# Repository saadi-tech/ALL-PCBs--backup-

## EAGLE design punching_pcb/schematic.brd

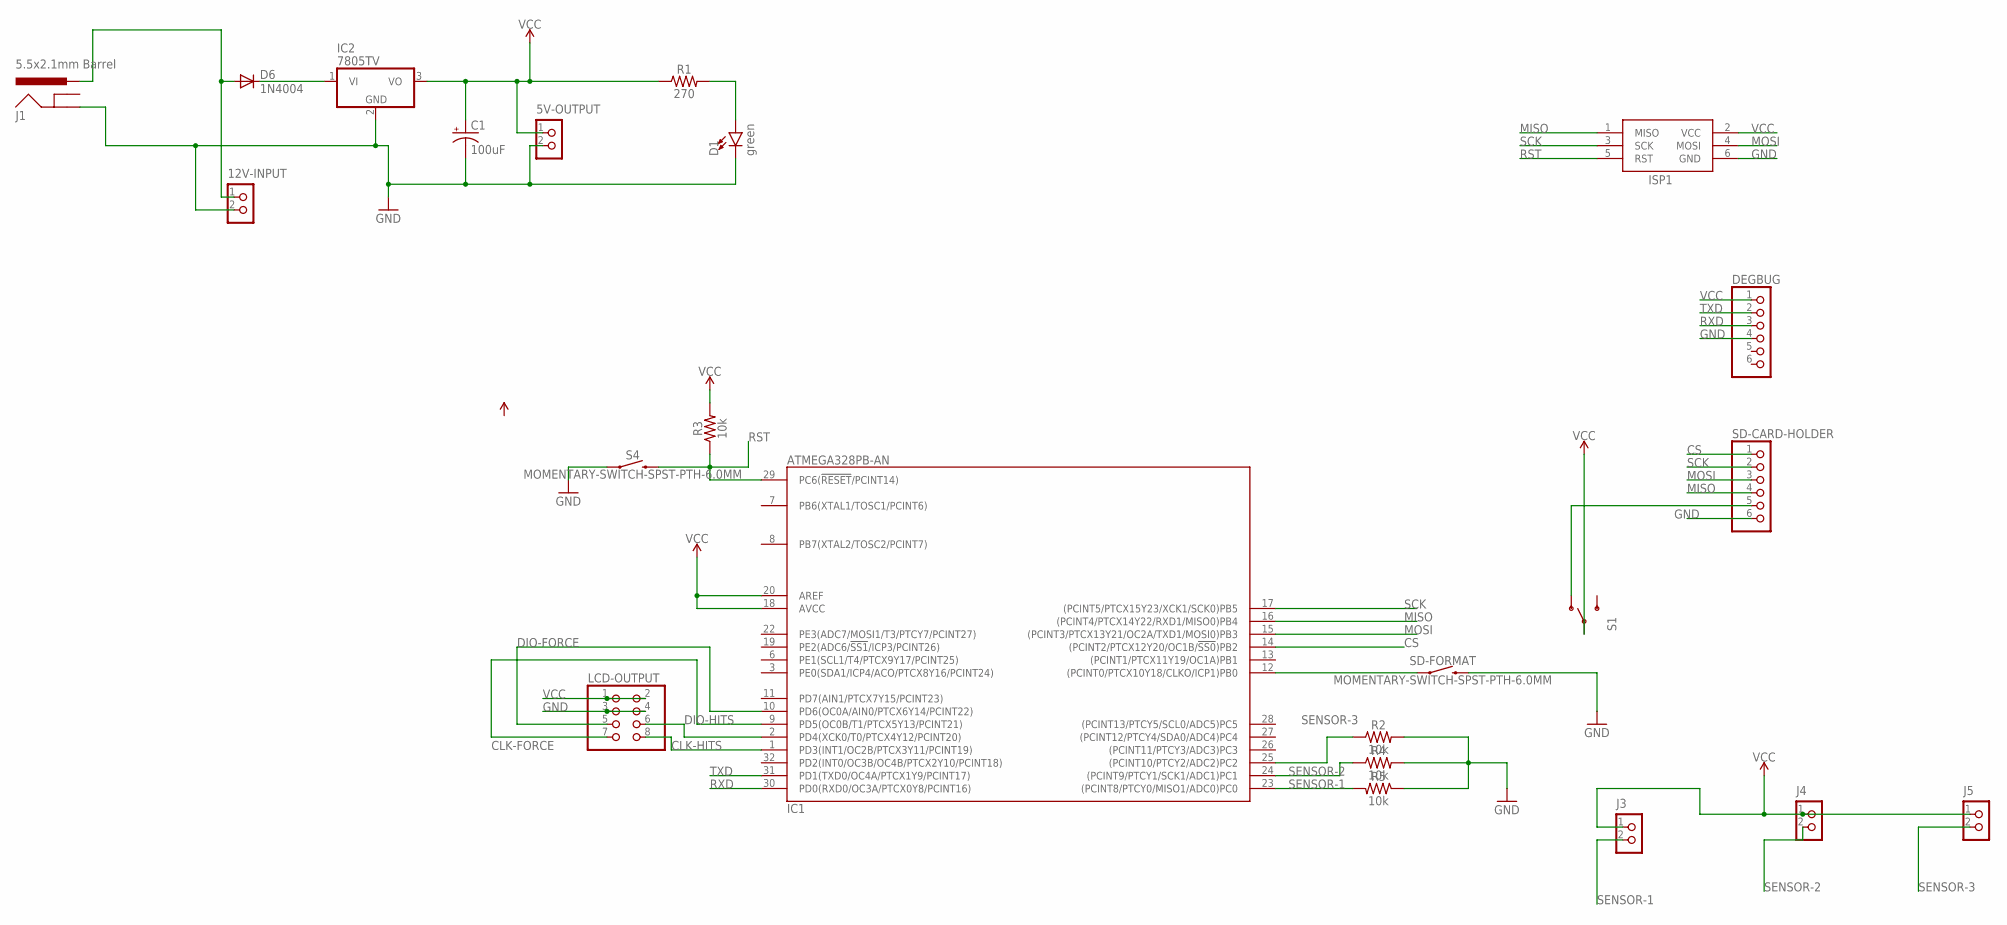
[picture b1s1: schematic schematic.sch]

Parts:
5V-OUTPUT, 12V-INPUT: CON_TERMINAL_BLOCK_02-5MM; TERMINAL_BLOCK_2P_5
C1: 100uF; CPOL-RADIAL-2.5MM-6.5MM
D1: green; LED-1206
D6: 1N4004; DO41-10
DEGBUG: PINHD-1X6; 1X06
IC1: ATMEGA328PB-AN; QFP32_7X7_0.80
IC2: 7805TV; TO220V
ISP1: AVRISP-6; AVRISP
J1: 5.5x2.1mm Barrel; POWER_JACK_SMD
J3, J4, J5: CON_TERMINAL_BLOCK_02-5MM; TERMINAL_BLOCK_2P_5
LCD-OUTPUT: PINHD-2X4; 2X04
R1: 270; 1206
R2, R3, R4, R5: 10k; 1206
S1: SWITCH-SPDTSMD; SWITCH_SPDT_SMD
S4: MOMENTARY-SWITCH-SPST-PTH-6.0MM; TACTILE_SWITCH_PTH_6.0MM
SD-CARD-HOLDER: PINHD-1X6; 1X06
SD-FORMAT: MOMENTARY-SWITCH-SPST-PTH-6.0MM; TACTILE_SWITCH_PTH_6.0MM

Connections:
CLK-FORCE: IC1.9 (PD5(OC0B/T1/PTCX5Y13/PCINT21)), LCD-OUTPUT.7
CLK-HITS: IC1.1 (PD3(INT1/OC2B/PTCX3Y11/PCINT19)), LCD-OUTPUT.8
CS: IC1.14 ((PCINT2/PTCX12Y20/OC1B/!SS0!)PB2), SD-CARD-HOLDER.1
DIO-FORCE: IC1.10 (PD6(OC0A/AIN0/PTCX6Y14/PCINT22)), LCD-OUTPUT.5
DIO-HITS: IC1.2 (PD4(XCK0/T0/PTCX4Y12/PCINT20)), LCD-OUTPUT.6
GND: 5V-OUTPUT.2, 12V-INPUT.2, C1.2 (-), D1.C, DEGBUG.4, IC1.5 (GND), IC1.21 (GND), IC2.2 (GND), ISP1.6 (GND), J1.P$4 (GND), LCD-OUTPUT.3, LCD-OUTPUT.4, R2.2, R4.2, R5.1, S4.1, SD-CARD-HOLDER.6, SD-FORMAT.3 (2)
MISO: IC1.16 ((PCINT4/PTCX14Y22/RXD1/MISO0)PB4), ISP1.1 (MISO), SD-CARD-HOLDER.4
MOSI: IC1.15 ((PCINT3/PTCX13Y21/OC2A/TXD1/MOSI0)PB3), ISP1.4 (MOSI), SD-CARD-HOLDER.3
unnamed: D1.A, R1.2
unnamed: IC1.12 ((PCINT0/PTCX10Y18/CLKO/ICP1)PB0), SD-FORMAT.1
unnamed: 12V-INPUT.1, D6.A, J1.VIN0 (PWR)
unnamed: D6.C, IC2.1 (VI)
unnamed: S1.1 (O), SD-CARD-HOLDER.5
RST: IC1.29 (PC6(!RESET!/PCINT14)), ISP1.5 (RST), R3.1, S4.3 (2)
RXD: DEGBUG.3, IC1.30 (PD0(RXD0/OC3A/PTCX0Y8/PCINT16))
SCK: IC1.17 ((PCINT5/PTCX15Y23/XCK1/SCK0)PB5), ISP1.3 (SCK), SD-CARD-HOLDER.2
SENSOR-1: IC1.23 ((PCINT8/PTCY0/MISO1/ADC0)PC0), J3.2, R5.2
SENSOR-2: IC1.24 ((PCINT9/PTCY1/SCK1/ADC1)PC1), J4.2, R4.1
SENSOR-3: IC1.25 ((PCINT10/PTCY2/ADC2)PC2), J5.2, R2.1
TXD: DEGBUG.2, IC1.31 (PD1(TXD0/OC4A/PTCX1Y9/PCINT17))
VCC: 5V-OUTPUT.1, C1.1 (+), DEGBUG.1, IC1.4 (VCC), IC1.18 (AVCC), IC1.20 (AREF), IC2.3 (VO), ISP1.2 (VCC), J3.1, J4.1, J5.1, LCD-OUTPUT.1, LCD-OUTPUT.2, R1.1, R3.2, S1.2

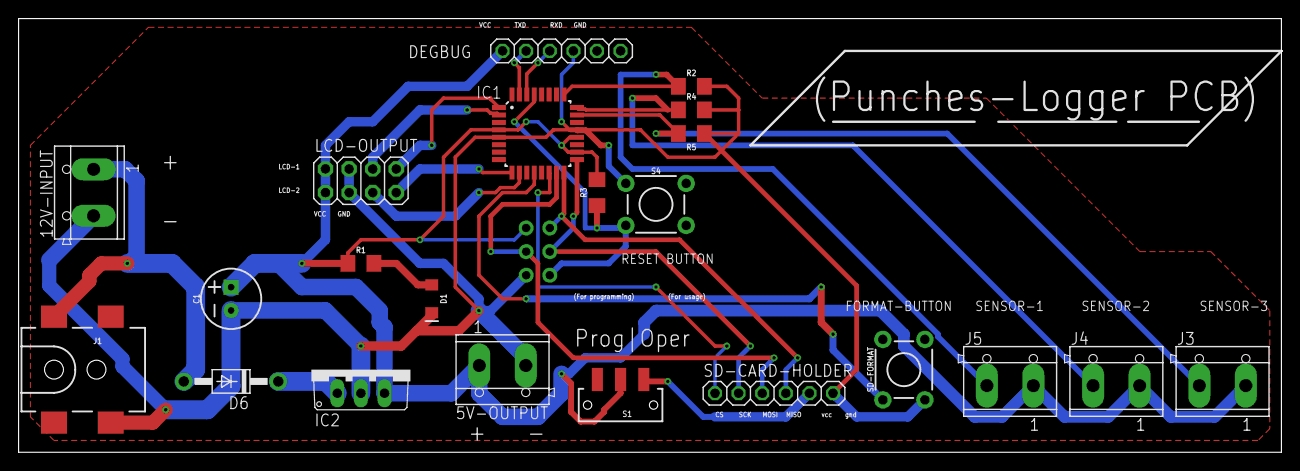
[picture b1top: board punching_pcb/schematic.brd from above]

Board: 2 copper layers, 135.9 x 46.7 mm, 23 parts (1 on the bottom side), 21 nets.

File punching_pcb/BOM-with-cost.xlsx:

Part;"Value";"Device";"Package";"Description";"POPULARITY";"PROD_ID";"SF_SKU";"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
5V-OUTPUT;"CON_TERMINAL_BLOCK_02-5MM";"CON_TERMINAL_BLOCK_02-5MM";"TERMINAL_BLO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
12V-INPUT;"CON_TERMINAL_BLOCK_02-5MM";"CON_TERMINAL_BLOCK_02-5MM";"TERMINAL_BLO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
C1;"100uF";"100UF-POLAR-RADIAL-2.5MM-25V-20%";"CPOL-RADIAL-2.5MM-6.5MM";"100碌F 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
D1;"green";"LED1206";"LED-1206";"LED (Generic)";"";"";"";"";
D6;"1N4004";"1N4004";"DO41-10";"DIODE";"";"";"";"";
DEGBUG;"";"PINHD-1X6";"1X06";"PIN HEADER";"";"";"";"";
IC1;"ATMEGA328PB-AN";"ATMEGA328PB-AN";"QFP32_7X7_0.80";"8-bit AVR Microcontroll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
IC2;"7805TV";"7805TV";"TO220V";"Positive VOLTAGE REGULATOR";"57";"";"";"";
ISP1;"AVRISP-6";"AVRISP-6";"AVRISP";"AVR ISP HEADER";"";"";"";"";
J3;"CON_TERMINAL_BLOCK_02-5MM";"CON_TERMINAL_BLOCK_02-5MM";"TERMINAL_BLOCK_2P_5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
J4;"CON_TERMINAL_BLOCK_02-5MM";"CON_TERMINAL_BLOCK_02-5MM";"TERMINAL_BLOCK_2P_5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
J5;"CON_TERMINAL_BLOCK_02-5MM";"CON_TERMINAL_BLOCK_02-5MM";"TERMINAL_BLOCK_2P_5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
J11;"POWER_JACK";"POWER_JACK";"POWER_JACK_PTH";"Power Jack Connector";"";"CONN-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
LCD-OUTPUT;"";"PINHD-2X4";"2X04";"PIN HEADER";"";"";"";"";
R1;"270";"RESISTOR1206";"1206";"Generic Resistor Package";"";" ";"";" ";
R2;"10k";"RESISTOR1206";"1206";"Generic Resistor Package";"";" ";"";" ";
R3;"10k";"RESISTOR1206";"1206";"Generic Resistor Package";"";" ";"";" ";
R4;"10k";"RESISTOR1206";"1206";"Generic Resistor Package";"";" ";"";" ";
R5;"10k";"RESISTOR1206";"1206";"Generic Resistor Package";"";" ";"";" ";
S1;"";"SWITCH-SPDTSMD";"SWITCH_SPDT_SMD";"SPDT Switch";"";"";"";"";
S4;"MOMENTARY-SWITCH-SPST-PTH-6.0MM";"MOMENTARY-SWITCH-SPST-PTH-6.0MM";"TACTILE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
SD-CARD-HOLDER;"";"PINHD-1X6";"1X06";"PIN HEADER";"";"";"";"";
SD-FORMAT;"MOMENTARY-SWITCH-SPST-PTH-6.0MM";"MOMENTARY-SWITCH-SPST-PTH-6.0MM";"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

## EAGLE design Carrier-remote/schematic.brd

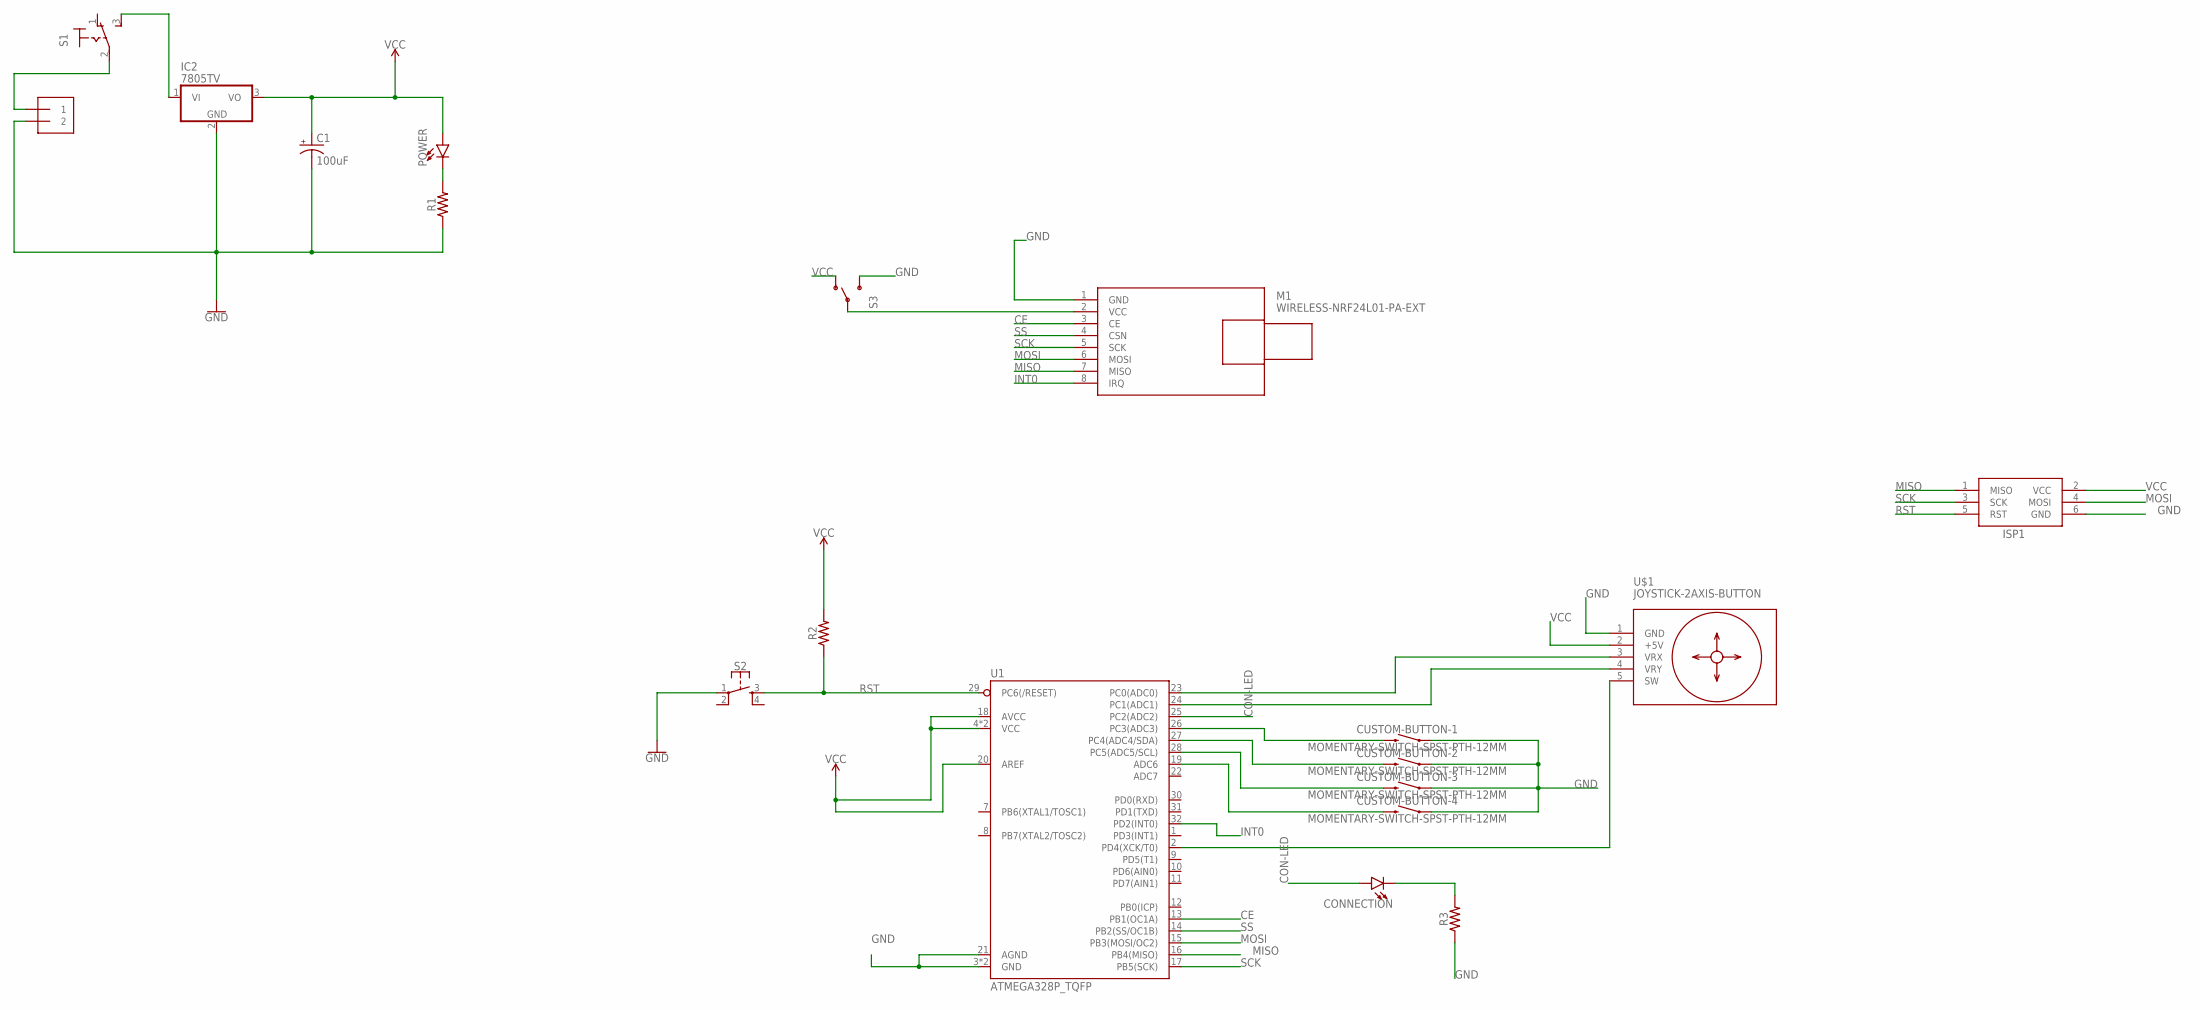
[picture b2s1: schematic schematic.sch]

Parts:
C1: 100uF; CPOL-RADIAL-2.5MM-6.5MM
CONNECTION: LED3MM; LED_3MM
CUSTOM-BUTTON-1, CUSTOM-BUTTON-2, CUSTOM-BUTTON-3, CUSTOM-BUTTON-4: MOMENTARY-SWITCH-SPST-PTH-12MM; TACTILE_SWITCH_PTH_12MM
IC2: 7805TV; TO220V
ISP1: AVRISP-6; AVRISP
J1: 1X2-3.5MM
M1: WIRELESS-NRF24L01-PA-EXT
POWER: LED3MM; LED_3MM
R1, R2, R3: 1206
S1: 320-916
S2: MOMENTARY-SWITCH-SPST-2-SMD-4.6X2.8MM; TACTILE_SWITCH_SMD_4.6X2.8MM
S3: SWITCH-SPDTSMD; SWITCH_SPDT_SMD
U1: ATMEGA328P_TQFP; TQFP32-08
U$1: JOYSTICK-2AXIS-BUTTON

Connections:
CE: M1.3 (CE), U1.13 (PB1(OC1A))
CON-LED: CONNECTION.A, U1.25 (PC2(ADC2))
GND: C1.2 (-), CUSTOM-BUTTON-1.1, CUSTOM-BUTTON-2.1, CUSTOM-BUTTON-3.1, CUSTOM-BUTTON-4.1, IC2.2 (GND), ISP1.6 (GND), J1.2, M1.1 (GND), R1.1, R3.1, S2.1, S3.3 (S), U1.3 (GND), U1.5 (GND), U1.21 (AGND), U$1.1 (GND)
INT0: M1.8 (IRQ), U1.32 (PD2(INT0))
MISO: ISP1.1 (MISO), M1.7 (MISO), U1.16 (PB4(MISO))
MOSI: ISP1.4 (MOSI), M1.6 (MOSI), U1.15 (PB3(MOSI/OC2))
unnamed: J1.1, S1.2
unnamed: IC2.1 (VI), S1.3 (S)
unnamed: POWER.K (C), R1.2
unnamed: M1.2 (VCC), S3.2
unnamed: CUSTOM-BUTTON-1.3 (2), U1.26 (PC3(ADC3))
unnamed: CUSTOM-BUTTON-2.3 (2), U1.27 (PC4(ADC4/SDA))
unnamed: U1.23 (PC0(ADC0)), U$1.3 (VRX)
unnamed: U1.24 (PC1(ADC1)), U$1.4 (VRY)
unnamed: U1.2 (PD4(XCK/T0)), U$1.5 (SW)
unnamed: CUSTOM-BUTTON-3.3 (2), U1.28 (PC5(ADC5/SCL))
unnamed: CUSTOM-BUTTON-4.3 (2), U1.19 (ADC6)
unnamed: CONNECTION.K (C), R3.2
RST: ISP1.5 (RST), R2.1, S2.3, U1.29 (PC6(/RESET))
SCK: ISP1.3 (SCK), M1.5 (SCK), U1.17 (PB5(SCK))
SS: M1.4 (CSN), U1.14 (PB2(SS/OC1B))
VCC: C1.1 (+), IC2.3 (VO), ISP1.2 (VCC), POWER.A, R2.2, S3.1 (O), U1.4 (VCC), U1.6 (VCC), U1.18 (AVCC), U1.20 (AREF), U$1.2 (+5V)

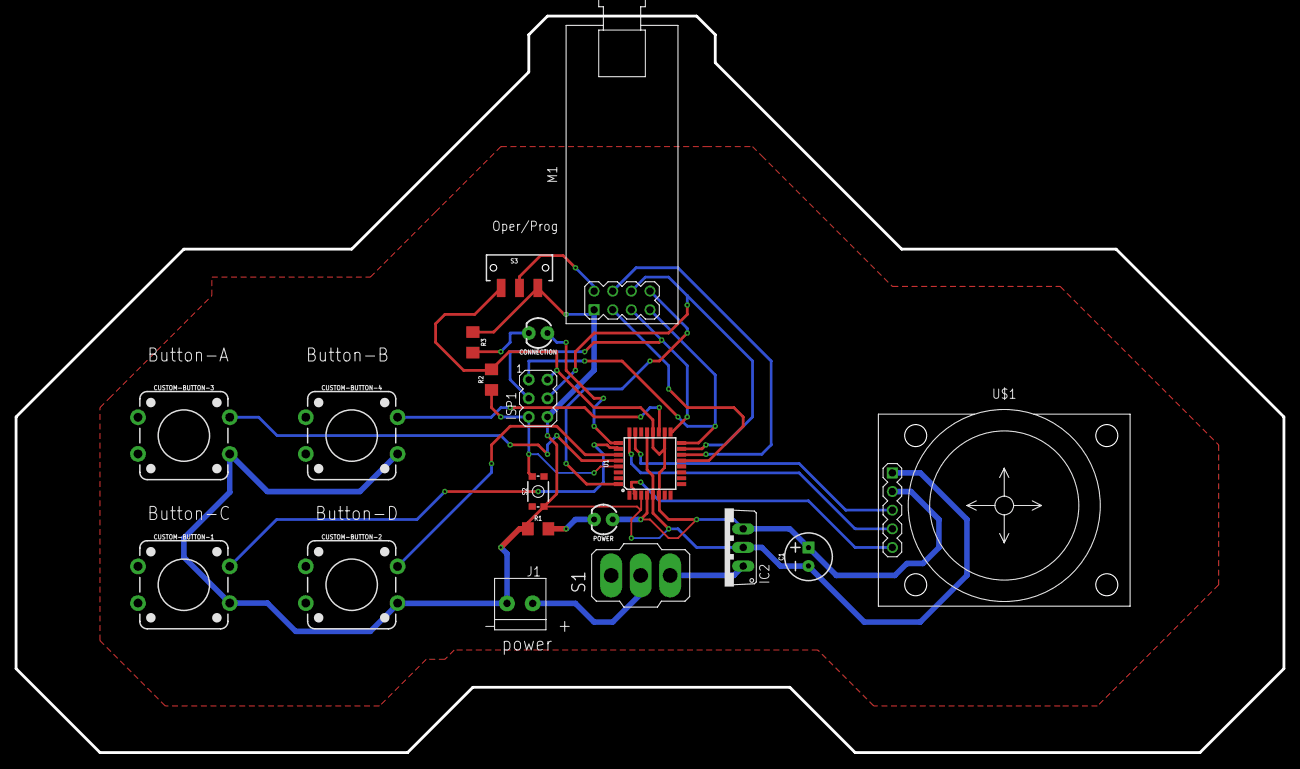
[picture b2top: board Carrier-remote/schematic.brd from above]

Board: 2 copper layers, 172.7 x 100.3 mm, 19 parts (0 on the bottom side), 22 nets.

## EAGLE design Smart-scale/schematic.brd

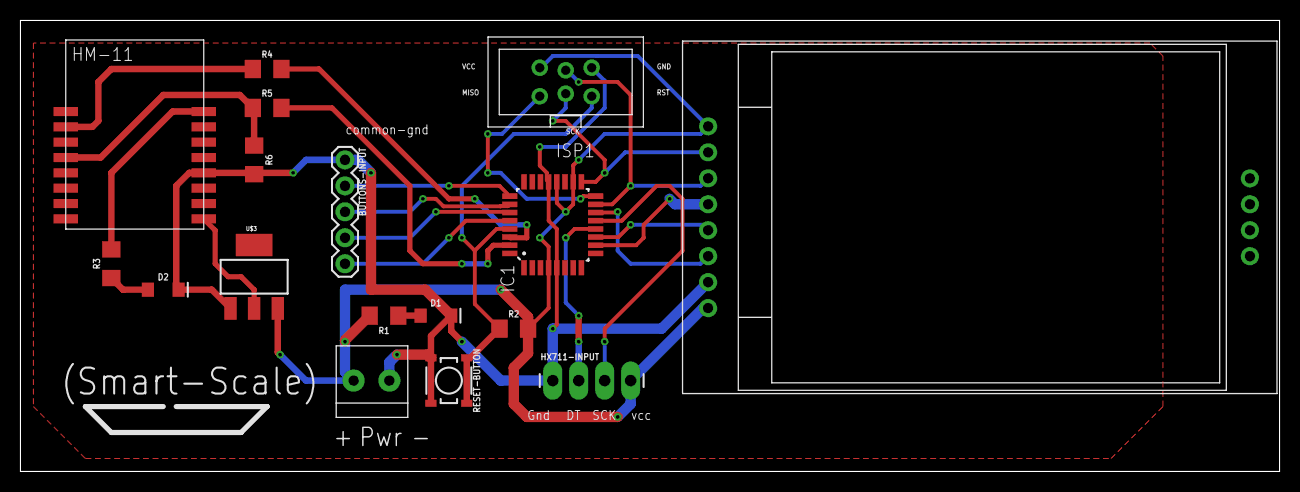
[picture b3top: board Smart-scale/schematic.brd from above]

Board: 2 copper layers, 123.2 x 44.1 mm, 17 parts (0 on the bottom side), 23 nets.

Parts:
BUTTONS-INPUT: 1X05
D1, D2: pwr_led; LED-1206
HX711-INPUT: 1X04_LONGPADS
IC1: ATMEGA328PB-AN; QFP32_7X7_0.80
ISP1: AVRISP-BOX
PWR: 1X2-3.5MM
R1, R3: 470; 1206
R2: 10k; 1206
R4, R5: 1k; 1206
R6: 2k; 1206
RESET-BUTTON: MOMENTARY-SWITCH-SPST-SMD-4.5MM; TACTILE_SWITCH_SMD_4.5MM
U$1: 1.8"_TFT
U$2: HM-11
U$3: V_REG_LD1117VXXLD1117-SMD; SOT223

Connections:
A0: IC1.10, U$1.P$12
BT_RX: IC1.31, R5.2
BT_TX: IC1.30, R4.2
GND: BUTTONS-INPUT.1, D1.C, D2.C, HX711-INPUT.1, IC1.5, IC1.21, ISP1.6, PWR.1, R6.2, RESET-BUTTON.2, RESET-BUTTON.3, U$1.P$15, U$2.GND, U$3.1
LCD_RST: IC1.11, U$1.P$13
MISO: IC1.16, ISP1.1
MOSI: IC1.15, ISP1.4, U$1.P$11
unnamed: U$2.VCC, U$3.2
unnamed: BUTTONS-INPUT.5, IC1.28
unnamed: D1.A, R1.1
unnamed: BUTTONS-INPUT.4, IC1.27
unnamed: BUTTONS-INPUT.3, IC1.26
unnamed: BUTTONS-INPUT.2, IC1.25
unnamed: HX711-INPUT.2, IC1.12
unnamed: HX711-INPUT.3, IC1.13
unnamed: R3.2, U$2.PIO0
unnamed: D2.A, R3.1
unnamed: R4.1, U$2.UART_TX
unnamed: R5.1, R6.1, U$2.UART_RX
RST: IC1.29, ISP1.5, R2.1, RESET-BUTTON.1, RESET-BUTTON.4
SCK: IC1.17, ISP1.3, U$1.P$10
SS: IC1.14, U$1.P$14
VCC: HX711-INPUT.4, IC1.4, IC1.18, IC1.20, ISP1.2, PWR.2, R1.2, R2.2, U$1.P$9, U$1.P$16, U$3.3

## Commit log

2020-11-18 ll pcb designs
2020-11-23 dd the PCB designs backup

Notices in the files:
parts and their libraries:
SparkFun-Capacitors: Licensing: Creative Commons ShareAlike 4.0 International - https://creativecommons.org/licenses/by-sa/4.0
diy-modules: Released under the Creative Commons Attribution 4.0 International License: http://creativecommons.org/licenses/by/4.0
